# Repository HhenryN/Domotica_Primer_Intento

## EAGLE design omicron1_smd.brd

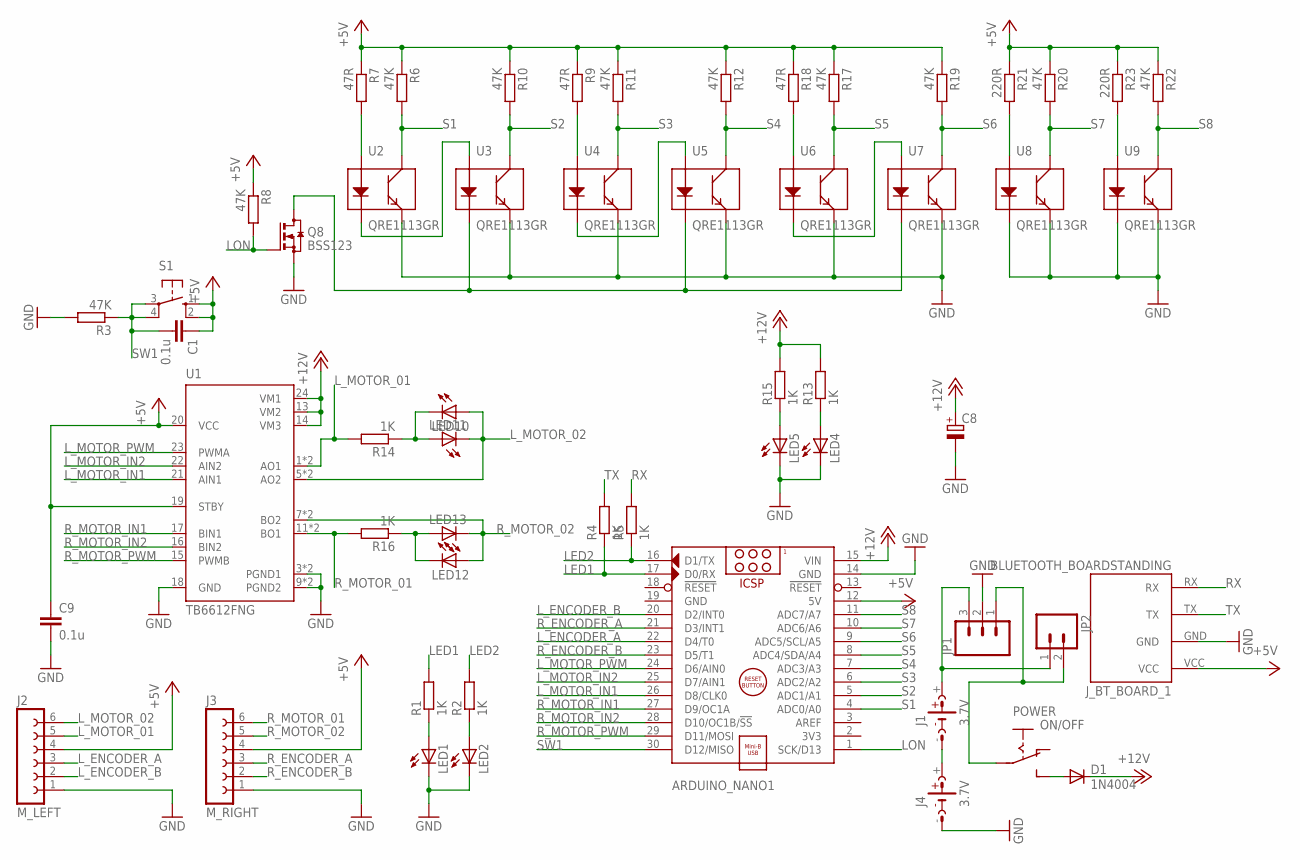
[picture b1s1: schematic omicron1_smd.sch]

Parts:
ARDUINO_NANO1: ARDUINO_NANO
C1, C9: 0.1u; C0805
C8: CPOL-EUE2,5-6E; E2,5-6E
D1: 1N4004; DO41-10
J1, J4: 3.7V; BATTERY
J2: M_LEFT; CON6-1_2MM
J3: M_RIGHT; CON6-1_2MM
JP1: M03PTH; 1X03
JP2: M02PTH; 1X02
J_BT_BOARD_1: BLUETOOTH_BOARDSTANDING; BT_BOARD_FOOTPRINT_STANDING
LED1, LED2, LED4, LED5, LED10, LED11, LED12, LED13: LEDCHIP-LED0805; CHIP-LED0805
POWER: ON/OFF; SWITCH
Q8: BSS123; SOT23
R1, R2, R4, R5, R13, R14, R15, R16: 1K; R0805
R3, R6, R8, R10, R11, R12, R17, R19, R20, R22: 47K; R0805
R7, R9, R18: 47R; R0805
R21, R23: 220R; R0805
S1: 10-XX; B3F-10XX
U1: TB6612FNG; SSOP24
U2, U3, U4, U5, U6, U7, U8, U9: QRE1113GR; QRE1113

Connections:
+5V: ARDUINO_NANO1.12 (5V), C1.1, C9.1, J2.4, J3.4, J_BT_BOARD_1.VCC, R6.1, R7.1, R8.1, R9.1, R10.1, R11.1, R12.1, R17.1, R18.1, R19.1, R20.1, R21.1, R22.1, R23.1, S1.1 (S), S1.2 (S1), U1.19 (STBY), U1.20 (VCC)
+12V: ARDUINO_NANO1.15 (VIN), C8.+, D1.C, R13.2, R15.2, U1.13 (VM2), U1.14 (VM3), U1.24 (VM1)
GND: ARDUINO_NANO1.14 (GND), ARDUINO_NANO1.19 (GND), C8.-, C9.2, J2.1, J3.1, J4.-, JP1.2, J_BT_BOARD_1.GND, LED1.C, LED2.C, LED4.C, LED5.C, Q8.2 (S), R3.2, U1.3 (PGND1), U1.4 (PGND1), U1.9 (PGND2), U1.10 (PGND2), U1.18 (GND), U2.4 (E), U3.4 (E), U4.4 (E), U5.4 (E), U6.4 (E), U7.4 (E), U8.2 (K), U8.4 (E), U9.2 (K), U9.4 (E)
LED1: ARDUINO_NANO1.17 (D0/RX), R1.2, R4.1
LED2: ARDUINO_NANO1.16 (D1/TX), R2.2, R5.1
LINE_K2: Q8.3 (D), U3.2 (K), U5.2 (K), U7.2 (K)
LON: ARDUINO_NANO1.1 (SCK/D13), Q8.1 (G), R8.2
L_ENCODER_A: ARDUINO_NANO1.22 (D4/T0), J2.3
L_ENCODER_B: ARDUINO_NANO1.20 (D2/INT0), J2.2
L_MOTOR_01: J2.5, R14.2, U1.1 (AO1), U1.2 (AO1)
L_MOTOR_02: J2.6, LED10.A, LED11.C, U1.5 (AO2), U1.6 (AO2)
L_MOTOR_IN1: ARDUINO_NANO1.26 (D8/CLK0), U1.21 (AIN1)
L_MOTOR_IN2: ARDUINO_NANO1.25 (D7/AIN1), U1.22 (AIN2)
L_MOTOR_PWM: ARDUINO_NANO1.24 (D6/AIN0), U1.23 (PWMA)
unnamed: R23.2, U9.1 (A)
unnamed: R21.2, U8.1 (A)
unnamed: J1.-, J4.+
unnamed: LED1.A, R1.1
unnamed: LED2.A, R2.1
unnamed: D1.A, POWER.S
unnamed: J1.+, JP1.3, JP2.1
unnamed: LED5.A, R15.1
unnamed: LED4.A, R13.1
unnamed: LED10.C, LED11.A, R14.1
unnamed: JP1.1, JP2.2, POWER.P
unnamed: LED12.C, LED13.A, R16.1
unnamed: R7.2, U2.1 (A)
unnamed: U2.2 (K), U3.1 (A)
unnamed: U4.2 (K), U5.1 (A)
unnamed: U6.2 (K), U7.1 (A)
unnamed: R18.2, U6.1 (A)
unnamed: R9.2, U4.1 (A)
RX: J_BT_BOARD_1.RX, R5.2
R_ENCODER_A: ARDUINO_NANO1.21 (D3/INT1), J3.3
R_ENCODER_B: ARDUINO_NANO1.23 (D5/T1), J3.2
R_MOTOR_01: J3.6, R16.2, U1.11 (BO1), U1.12 (BO1)
R_MOTOR_02: J3.5, LED12.A, LED13.C, U1.7 (BO2), U1.8 (BO2)
R_MOTOR_IN1: ARDUINO_NANO1.27 (D9/OC1A), U1.17 (BIN1)
R_MOTOR_IN2: ARDUINO_NANO1.28 (D10/OC1B/!SS), U1.16 (BIN2)
R_MOTOR_PWM: ARDUINO_NANO1.29 (D11/MOSI), U1.15 (PWMB)
S1: ARDUINO_NANO1.4 (ADC0/A0), R6.2, U2.3 (C)
S2: ARDUINO_NANO1.5 (ADC1/A1), R10.2, U3.3 (C)
S3: ARDUINO_NANO1.6 (ADC2/A2), R11.2, U4.3 (C)
S4: ARDUINO_NANO1.7 (ADC3/A3), R12.2, U5.3 (C)
S5: ARDUINO_NANO1.8 (ADC4/SDA/A4), R17.2, U6.3 (C)
S6: ARDUINO_NANO1.9 (ADC5/SCL/A5), R19.2, U7.3 (C)
S7: ARDUINO_NANO1.10 (ADC6/A6), R20.2, U8.3 (C)
S8: ARDUINO_NANO1.11 (ADC7/A7), R22.2, U9.3 (C)
SW1: ARDUINO_NANO1.30 (D12/MISO), C1.2, R3.1, S1.3, S1.4 (P1)
TX: J_BT_BOARD_1.TX, R4.2

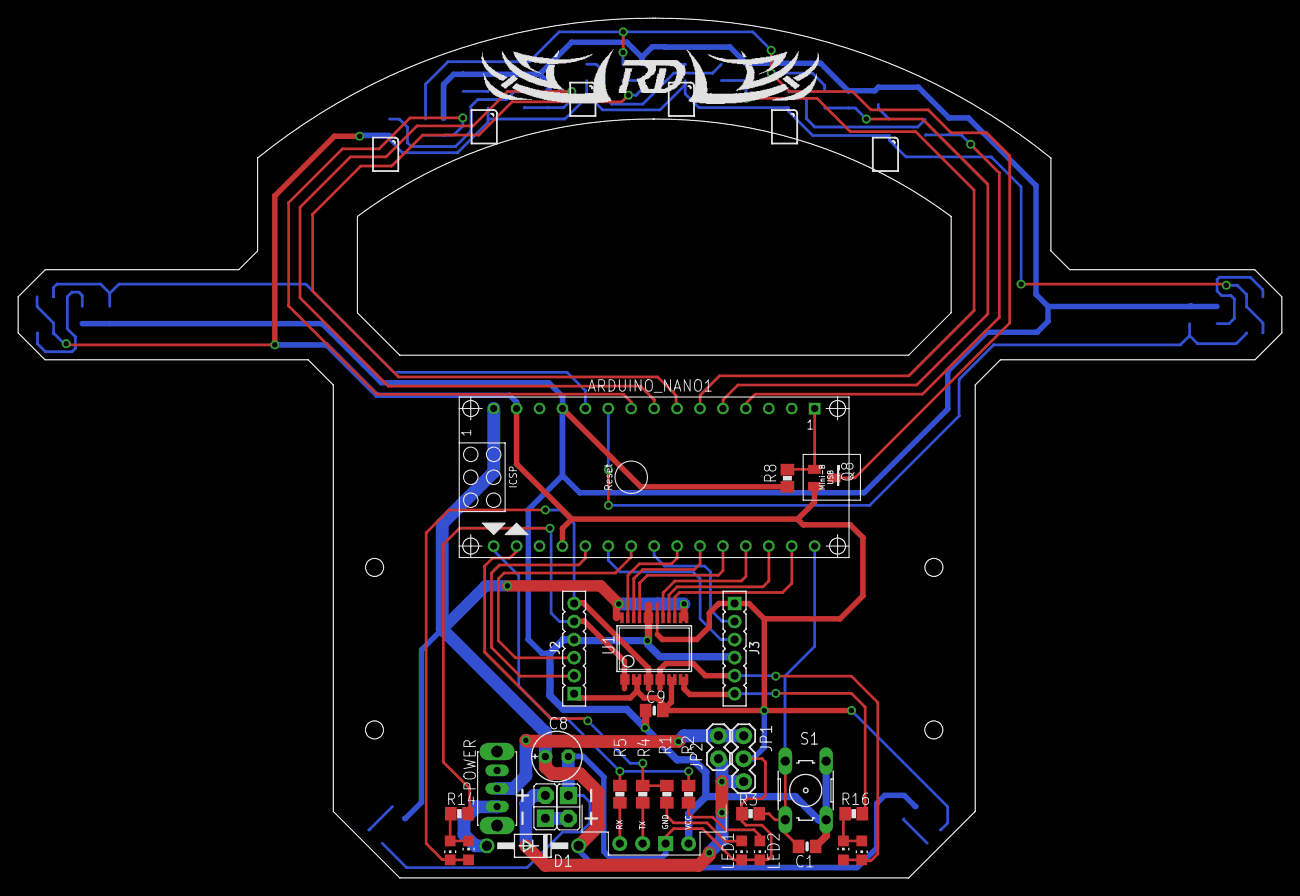
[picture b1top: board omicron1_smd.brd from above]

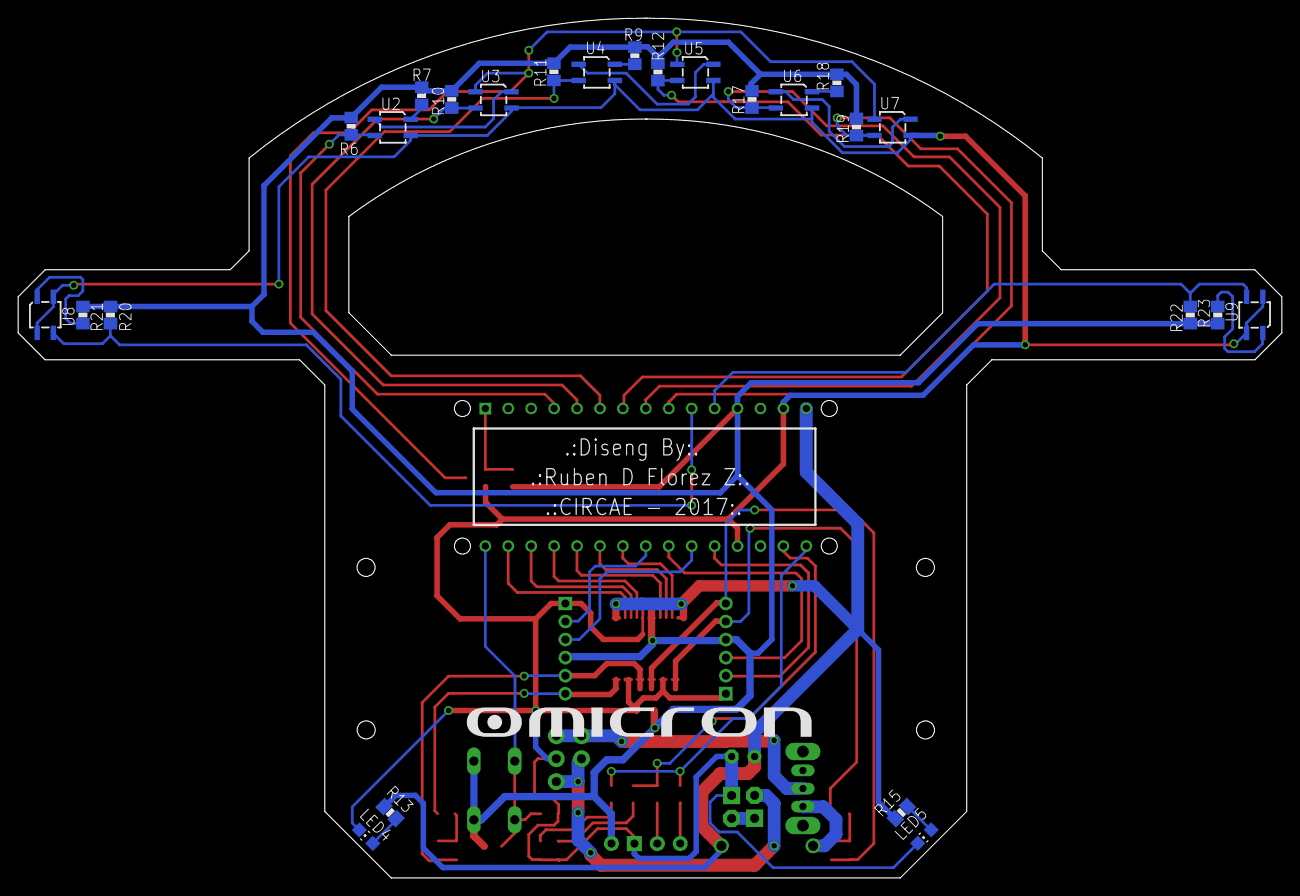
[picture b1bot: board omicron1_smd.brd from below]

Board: 2 copper layers, 140.0 x 95.2 mm, 55 parts (25 on the bottom side), 50 nets.

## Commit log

2018-03-17 Add files via upload
    pcb's robottracer
2018-03-17 Add files via upload
    comandos github
2018-03-17 HolaMundo Yhomira
2018-03-17 hola mundo
2018-03-17 HolaMundo_Yhomira
2018-03-17 hola mundo rama
2018-03-17 Hola_yhomira
2018-03-17 hello world

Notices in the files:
parts and their libraries:
SparkFun: Licensing: CC v3.0 Share-Alike You are welcome to use this library for commercial purposes.
